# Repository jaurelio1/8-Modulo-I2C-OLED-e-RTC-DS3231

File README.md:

# 8-Modulo-I2C-OLED-e-RTC-DS3231
Repositório da disciplina de Técnicas de Protipagem:

Alunos:

- José Aurélio
- Rennan Ramos
- Wesley Palmeira

Curso: Engenharia da Computação

DESPERTADOR

(exemplo)

O projeto em o intuido de prototipar um despertador fazendo o uso dos módulos I2C OLED e RTC DS3231
Utilizando o RTC(Real Time Clock) DS3231 que é um relógio em tempo real de alta precisão e baixo consumo de energia, podendo fornecer informações de hora, segundos, dia, mês e ano, junto com uma bateria CR2032 para permitir o armazenamentos dos dados mesmo com a falta de energia, evitando que dados sejam perdidos; O Atmega328p como microcontrolador; o SSD1306 display OLED com o módulo I2C; Buzzer ativo 5V.

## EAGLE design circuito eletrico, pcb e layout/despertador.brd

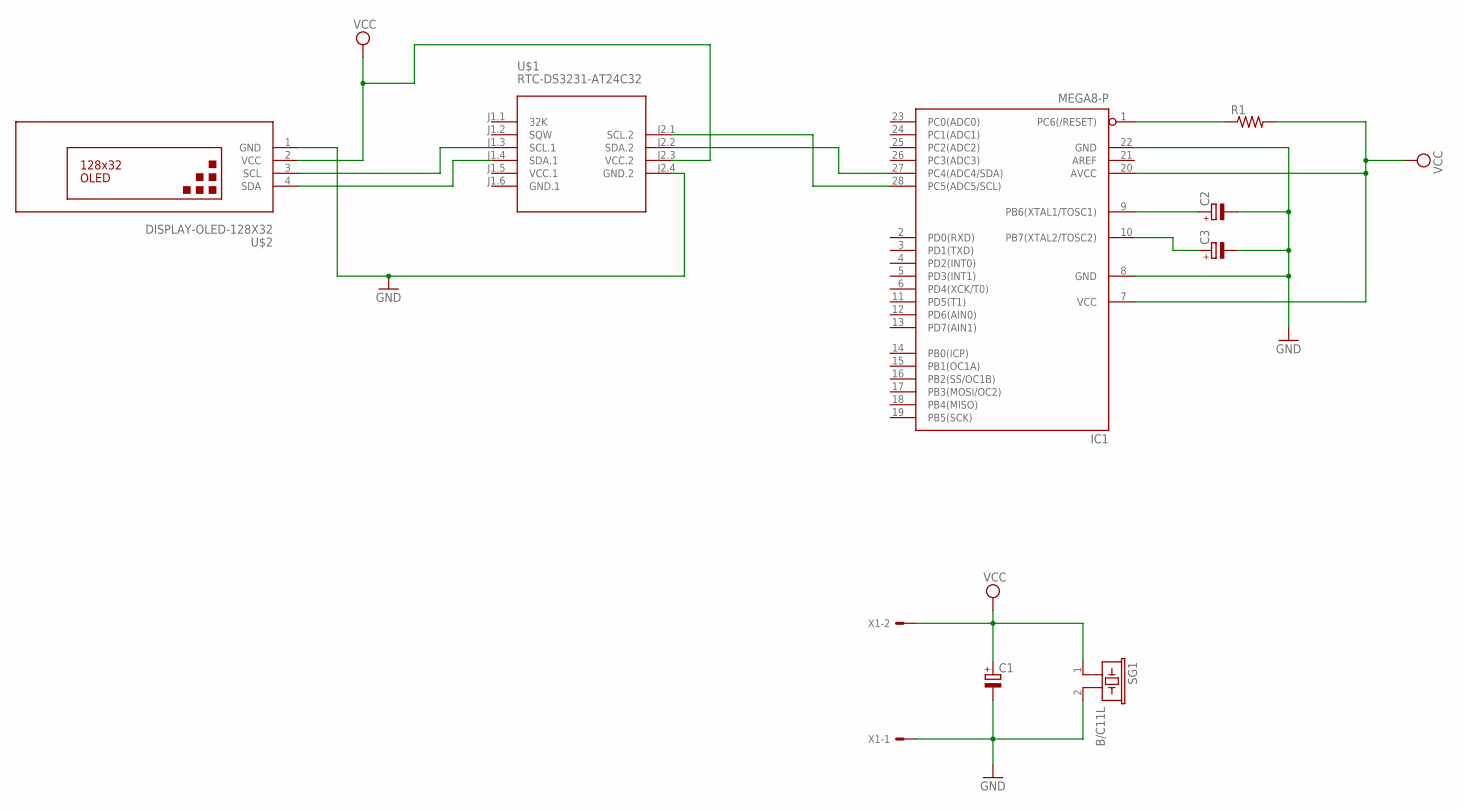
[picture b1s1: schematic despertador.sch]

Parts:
C1, C2, C3: CPOL-EUE2.5-6; E2,5-6
IC1: MEGA8-P; DIL28-3
R1: R-US_0207/10; 0207/10
SG1: B/C11L
U$1: RTC-DS3231-AT24C32
U$2: DISPLAY-OLED-128X32
X1: KK-156-2

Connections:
GND: C1.-, C2.-, C3.-, IC1.8 (GND), IC1.22 (GND), SG1.2, U$1.J2.4 (GND.2), U$2.1 (GND), X1.1
GND.1: U$1.J1.6 (GND.1)
unnamed: IC1.27 (PC4(ADC4/SDA)), U$1.J2.2 (SDA.2)
unnamed: C2.+, IC1.9 (PB6(XTAL1/TOSC1))
unnamed: C3.+, IC1.10 (PB7(XTAL2/TOSC2))
unnamed: IC1.1 (PC6(/RESET)), R1.1
unnamed: IC1.28 (PC5(ADC5/SCL)), U$1.J2.1 (SCL.2)
unnamed: U$1.J1.4 (SDA.1), U$2.4 (SDA)
unnamed: U$1.J1.3 (SCL.1), U$2.3 (SCL)
VCC: C1.+, IC1.7 (VCC), IC1.20 (AVCC), R1.2, SG1.1, U$1.J2.3 (VCC.2), U$2.2 (VCC), X1.2
VCC.1: U$1.J1.5 (VCC.1)

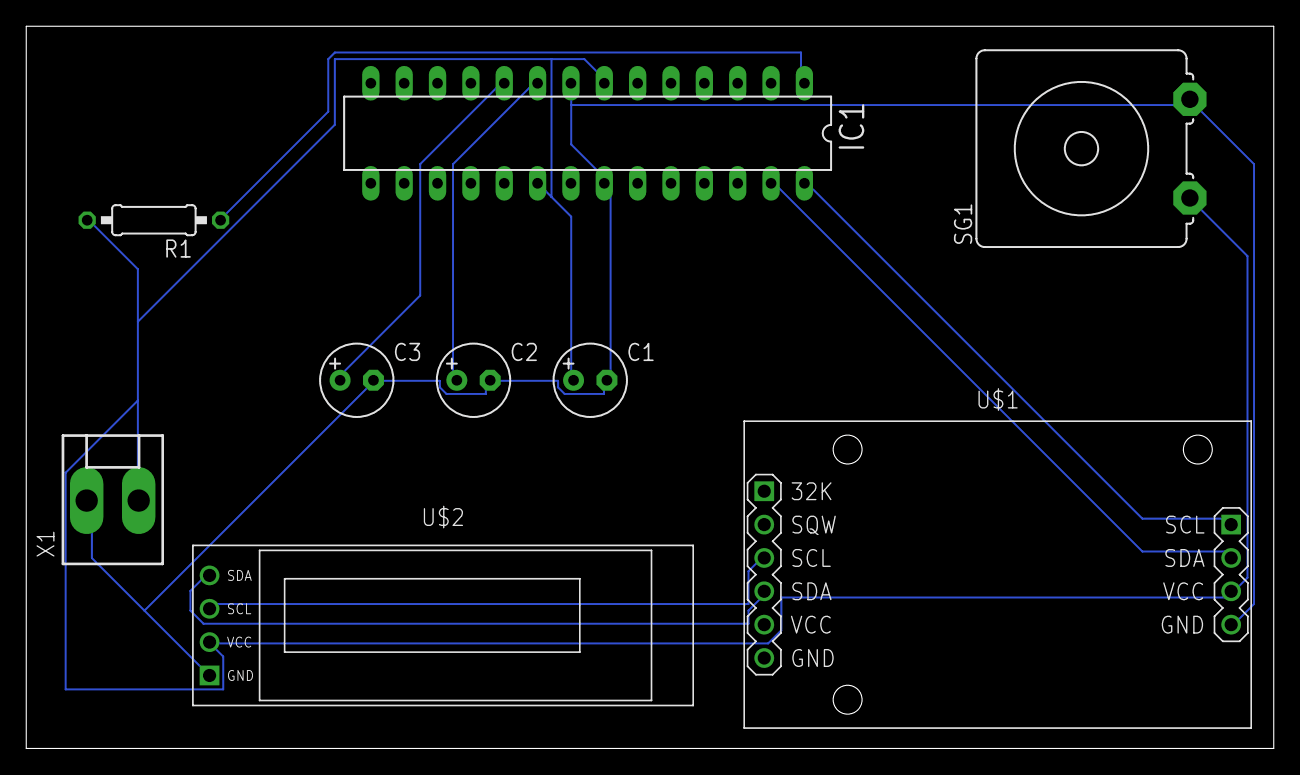
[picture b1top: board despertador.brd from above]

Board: 2 copper layers, 95.0 x 55.0 mm, 9 parts (0 on the bottom side), 9 nets.

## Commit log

2021-08-06 Adicionado datasheets dos componentes
2021-08-06 Modificado datasheet do OLED
2021-10-11 Adicionado arquivos do Fusion e PrusaSlicer
2021-10-15 Adicionado USB nos componentes
2021-10-20 Adicionado video

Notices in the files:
parts and their libraries:
diy-modules: Released under the Creative Commons Attribution 4.0 International License: http://creativecommons.org/licenses/by/4.0
